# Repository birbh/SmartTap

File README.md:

# SmartTap

SmartTap is a sleek, credit card thin(.8mm) personal card powered entirely by NFC and its energy harvesting tech. i.e no battery required!!!

## Overview:
SmartTap is a custom engineered PCB business card which is designed to make a great first impression among colleagues. It's equipped with an "NXP NT3H1101" energy harvesting NFC chip with an integrated PCB trace antenna coil and active indicator leds, the card wirelessly harvests power directly from any smartphone or NFC reader to illuminate upon tapping.

### What makes it unique?

- Zero external power: Operates completely wirelessly and without a battery!! It's done by harvesting 13.56 MHz RF energy from a phone's NFC field. 

- Credit card form factor: It's engineered at custom 0.8 mm thicknes, perfectly matching the ISO 7810 ID-1 standard for standard credit cards. 

- Aesthetic Silver Trace: Designed with exposed custom coil loops finished in smooth Lead-free HASL for high quality durability and sleek look against a matte black soldermask. 

- Instant Contact Sharing: Embedded NTAG I2C functionality which prompts to open digital portfolio links on modern nfc supported devices. If any device has no nfc compatibility, then I have attached a qr code to linktr.ee as to let everyone access my portfolio and know abt me. 

### Why I made it?

The standard paper business cards are very easy to lose, forget or throw away. So I awnted to design a physical hardware project that combines embedded engineering, PCB antenna design and a personal branding to an unforgettable hands-on experience. 

Also who wants a boring paper businesss card nowdays in the era or modern tech. So I developed this idea to leave our techy impression whenever we meet a person or go somewhere. Actually it helps us to farm some aura in front of our fellow friends😝.......jk. 

Creating this card solved two main challenges for me:
1. Learning hoow to design RF trace coils and passive energy harvesting power stages without needing bulky batteries. 
2. Creating a clean, modern networking tool that lets me share my work, social links, and contact info instantly with simple smartphone tap. 

### How to use it?

1. Take a mobilephone that supports NFC. 
2. Tap the card: 
    Bring your phone's NFC reader area(usually on top rear of iphones, center/top of android phones) close to the nfc coil area of the business card. 
3. Watch it light up: 
    The harvesting circuit draws power wirelessly from the phone's field and instantly lights up the onboard leds. 
4. Open Portfolio: 
    A notification will pop up instantly on your phone screen. Tap it to view my cintct details and online portfolio!!!
5. For those who dont have a nfc supported mobilephone, there is a qr code in the pcb's silkscreen which opens the same link as the nfc chip does. 

### Visuals in pcb:

1. Front:
    In the front part I have added my personal data like github,insta and linkedin along with my name. I have also added cool floral design in the silkscreen too which has leds embedded in its different vacant spaces. This has made my design more cool to look for a stranger.        

2. Back:
    Its the back part where the brain of my pcb is located. On the left side of my pcb there is a coil made with wire which helps to capture the nfc field of phone and convert it into electrical energy which is connected to NT3H1101W0FTTJ nfc chip module which then helps to light up the led in the front. Also there's a cool floral design along with an art of lord Krishna which has made my pcb more attractive. And there are some details abt me and a qr code linking to linktree as I have stated above.
    And I have planned to cover the copper coil with Lead-free HASL which would make my pcb look more attractive and cool. 
    
## Instruction to make this project:

Setting up and assembling the card is straightfoward:

### 1. PCB manufacturing specs:
When submitting the greber files to your pcb manufacturer, ensure the following settings are specifies:
- Board Thickness: 0.8 mm (which is crucial for credit card flexibility and thickness)
- Solder mask color: Matte black or black
- Silkscreen color: White
- Surface finish: Lead-Free HASL
- Copper weight: 1oz

### 2. SMT component soldering:
1. Clean the PCB pads with isopropyl alcohol(if available) before soldering. 
2. NFC IC(U1- NT3H1101): Align pins using the indicator in silkscreen. Apply flux and reflow using hot air station or a fine tip soldering iron. 
3. Passive Components: Solder the 100nf decoupling capacitor across VOUT and VSS, followed by the 33 ohm curreny limiting resistors. 
4. LED orientation: Check the polarity on the back of the 0603 SMD leds(red led preferred) before soldering to ensure correct polarity. 
5. Also make sure that you don't erase or damage the silkscreen data as there's a qr code in it and erasing it may corrupt the data. 

### 3. Programming the NT3H1101W0FTTJ data:
No external programmer or hardware flasher is required!!!
1. Download NFC Tools(available for free on [ios](https://apps.apple.com/np/app/ntag-i2c-demoboard/id1495775864) and [android](https://play.google.com/store/apps/details?id=com.nxp.nfc.tagwriter)).
2. Open the app, select "Write", and add your record (eg. URL Link,vCard or social media handle). 
3. Tap "Write" and hold the PCB card near your phone to save your digital information directly ti onboard chip. 

## Photos:
### CAD:
1. PCB:

2. LED:

3. Capacitor:

4. NT3H1101W0FTTJ nfc chip:

5. Resistor:

### Schematic:

### PCB:

## BOM(initial):

|Reference  |Qty|Value         |Footprint                         |Description          |Price(total)(with delivery)|Link                     |
|-----------|---|--------------|----------------------------------|---------------------|---------------------------|-------------------------|
|C1         |1  |100nf         |Capacitor_SMD:C_0603_1608Metric   |Unpolarized capacitor|~$6.5                      |https://shorturl.at/pb3hk|
|D1,D2,D3,D4|4  |LED           |LED_SMD:LED_0603_1608Metric       |Light emitting diode |~$5.4                      |https://shorturl.at/OBKqx|
|R1,R2,R3,R4|4  |33R           |Resistor_SMD:R_0603_1608Metric    |Resistor             |$5.5                       |https://shorturl.at/QddhA|
|U1         |1  |NT3H1101W0FTTJ|NT3H1101W0FTTJ:TSSOP8_SOT505-1_NXP|NFC chip             |~$28                       |https://shorturl.at/ylJg6|
|Total      |   |              |                                  |                     |~$48                       |                         |

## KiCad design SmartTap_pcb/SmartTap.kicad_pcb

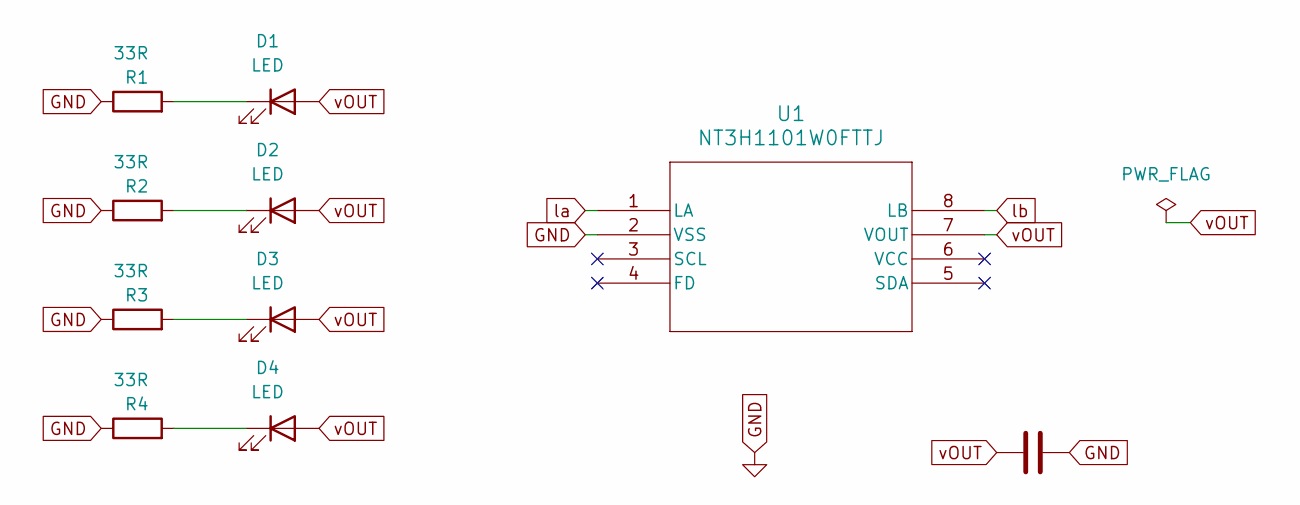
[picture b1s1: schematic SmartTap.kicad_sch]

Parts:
C1: 100nf; C_0603_1608Metric
D1, D2, D3, D4: LED; LED_0603_1608Metric
R1, R2, R3, R4: 33R; R_0603_1608Metric
U1: NT3H1101W0FTTJ; TSSOP8_SOT505-1_NXP

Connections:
GND: C1.2, R1.1, R2.1, R3.1, R4.1, U1.2 (VSS)
unnamed: D1.1 (K), R1.2
unnamed: D2.1 (K), R2.2
unnamed: D3.1 (K), R3.2
unnamed: D4.1 (K), R4.2
la: U1.1 (LA)
lb: U1.8 (LB)
vOUT: C1.1, D1.2 (A), D2.2 (A), D3.2 (A), D4.2 (A), U1.7 (VOUT)

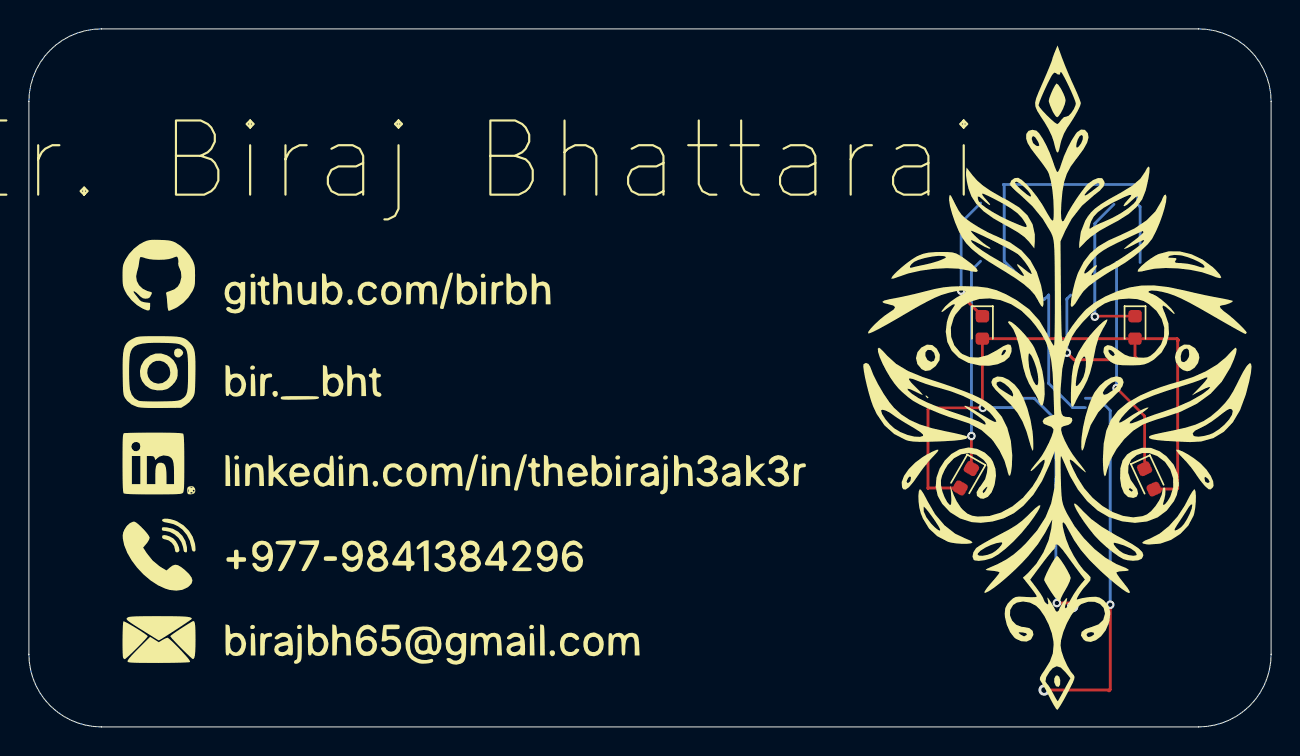
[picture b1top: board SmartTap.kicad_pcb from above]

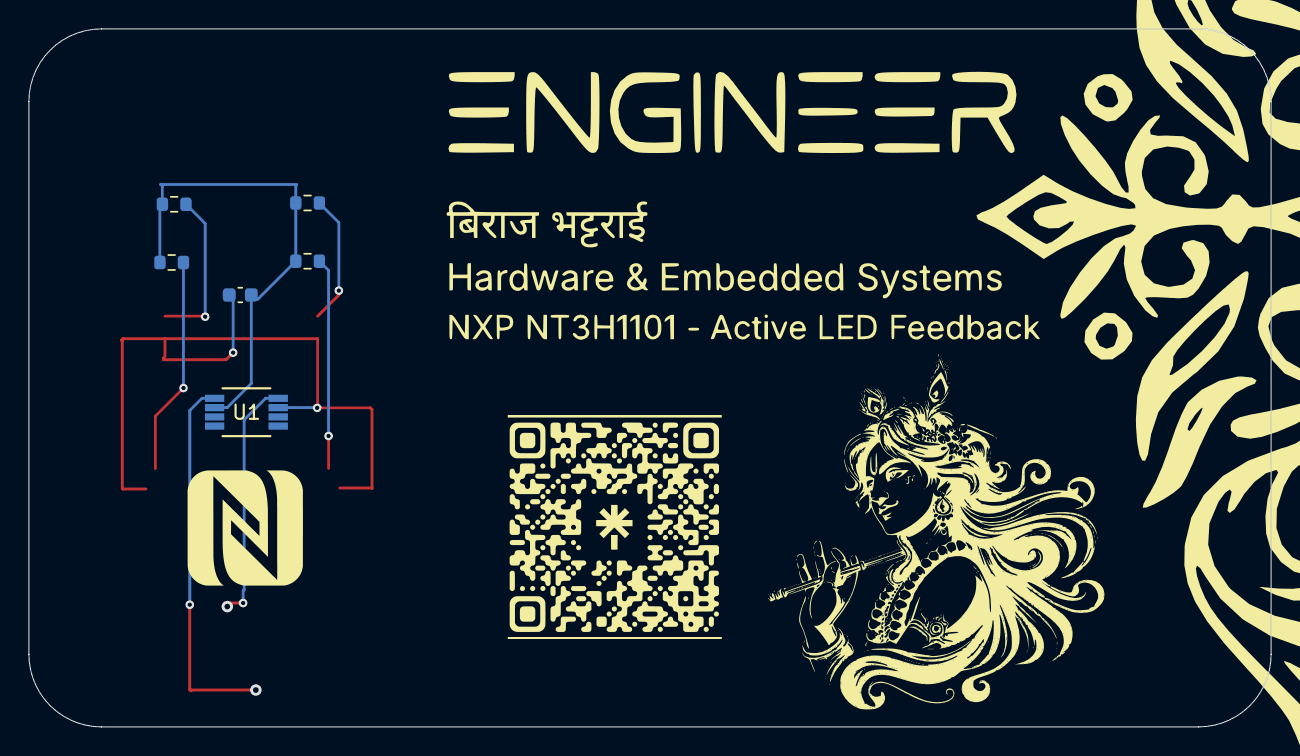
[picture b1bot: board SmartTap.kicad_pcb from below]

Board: 2 copper layers, 87.1 x 48.9 mm, 10 parts (6 on the bottom side), 6 nets.

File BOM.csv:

"Reference","Qty","Value","Footprint","Description",Price(total),Link
"C1","1","100nf","Capacitor_SMD:C_0603_1608Metric","Unpolarized capacitor",~$5,https://rb.gy/pjl6ke
"D1,D2,D3,D4","4","LED","LED_SMD:LED_0603_1608Metric","Light emitting diode",~$9,https://h1.nu/1vUUt
"R1,R2,R3,R4","4","33R","Resistor_SMD:R_0603_1608Metric","Resistor",$5,https://h1.nu/1BzlD
"U1","1","NT3H1101W0FTTJ","NT3H1101W0FTTJ:TSSOP8_SOT505-1_NXP","NFC chip",~$2,https://h1.nu/1vUZM
Total,,,,,~$22,
